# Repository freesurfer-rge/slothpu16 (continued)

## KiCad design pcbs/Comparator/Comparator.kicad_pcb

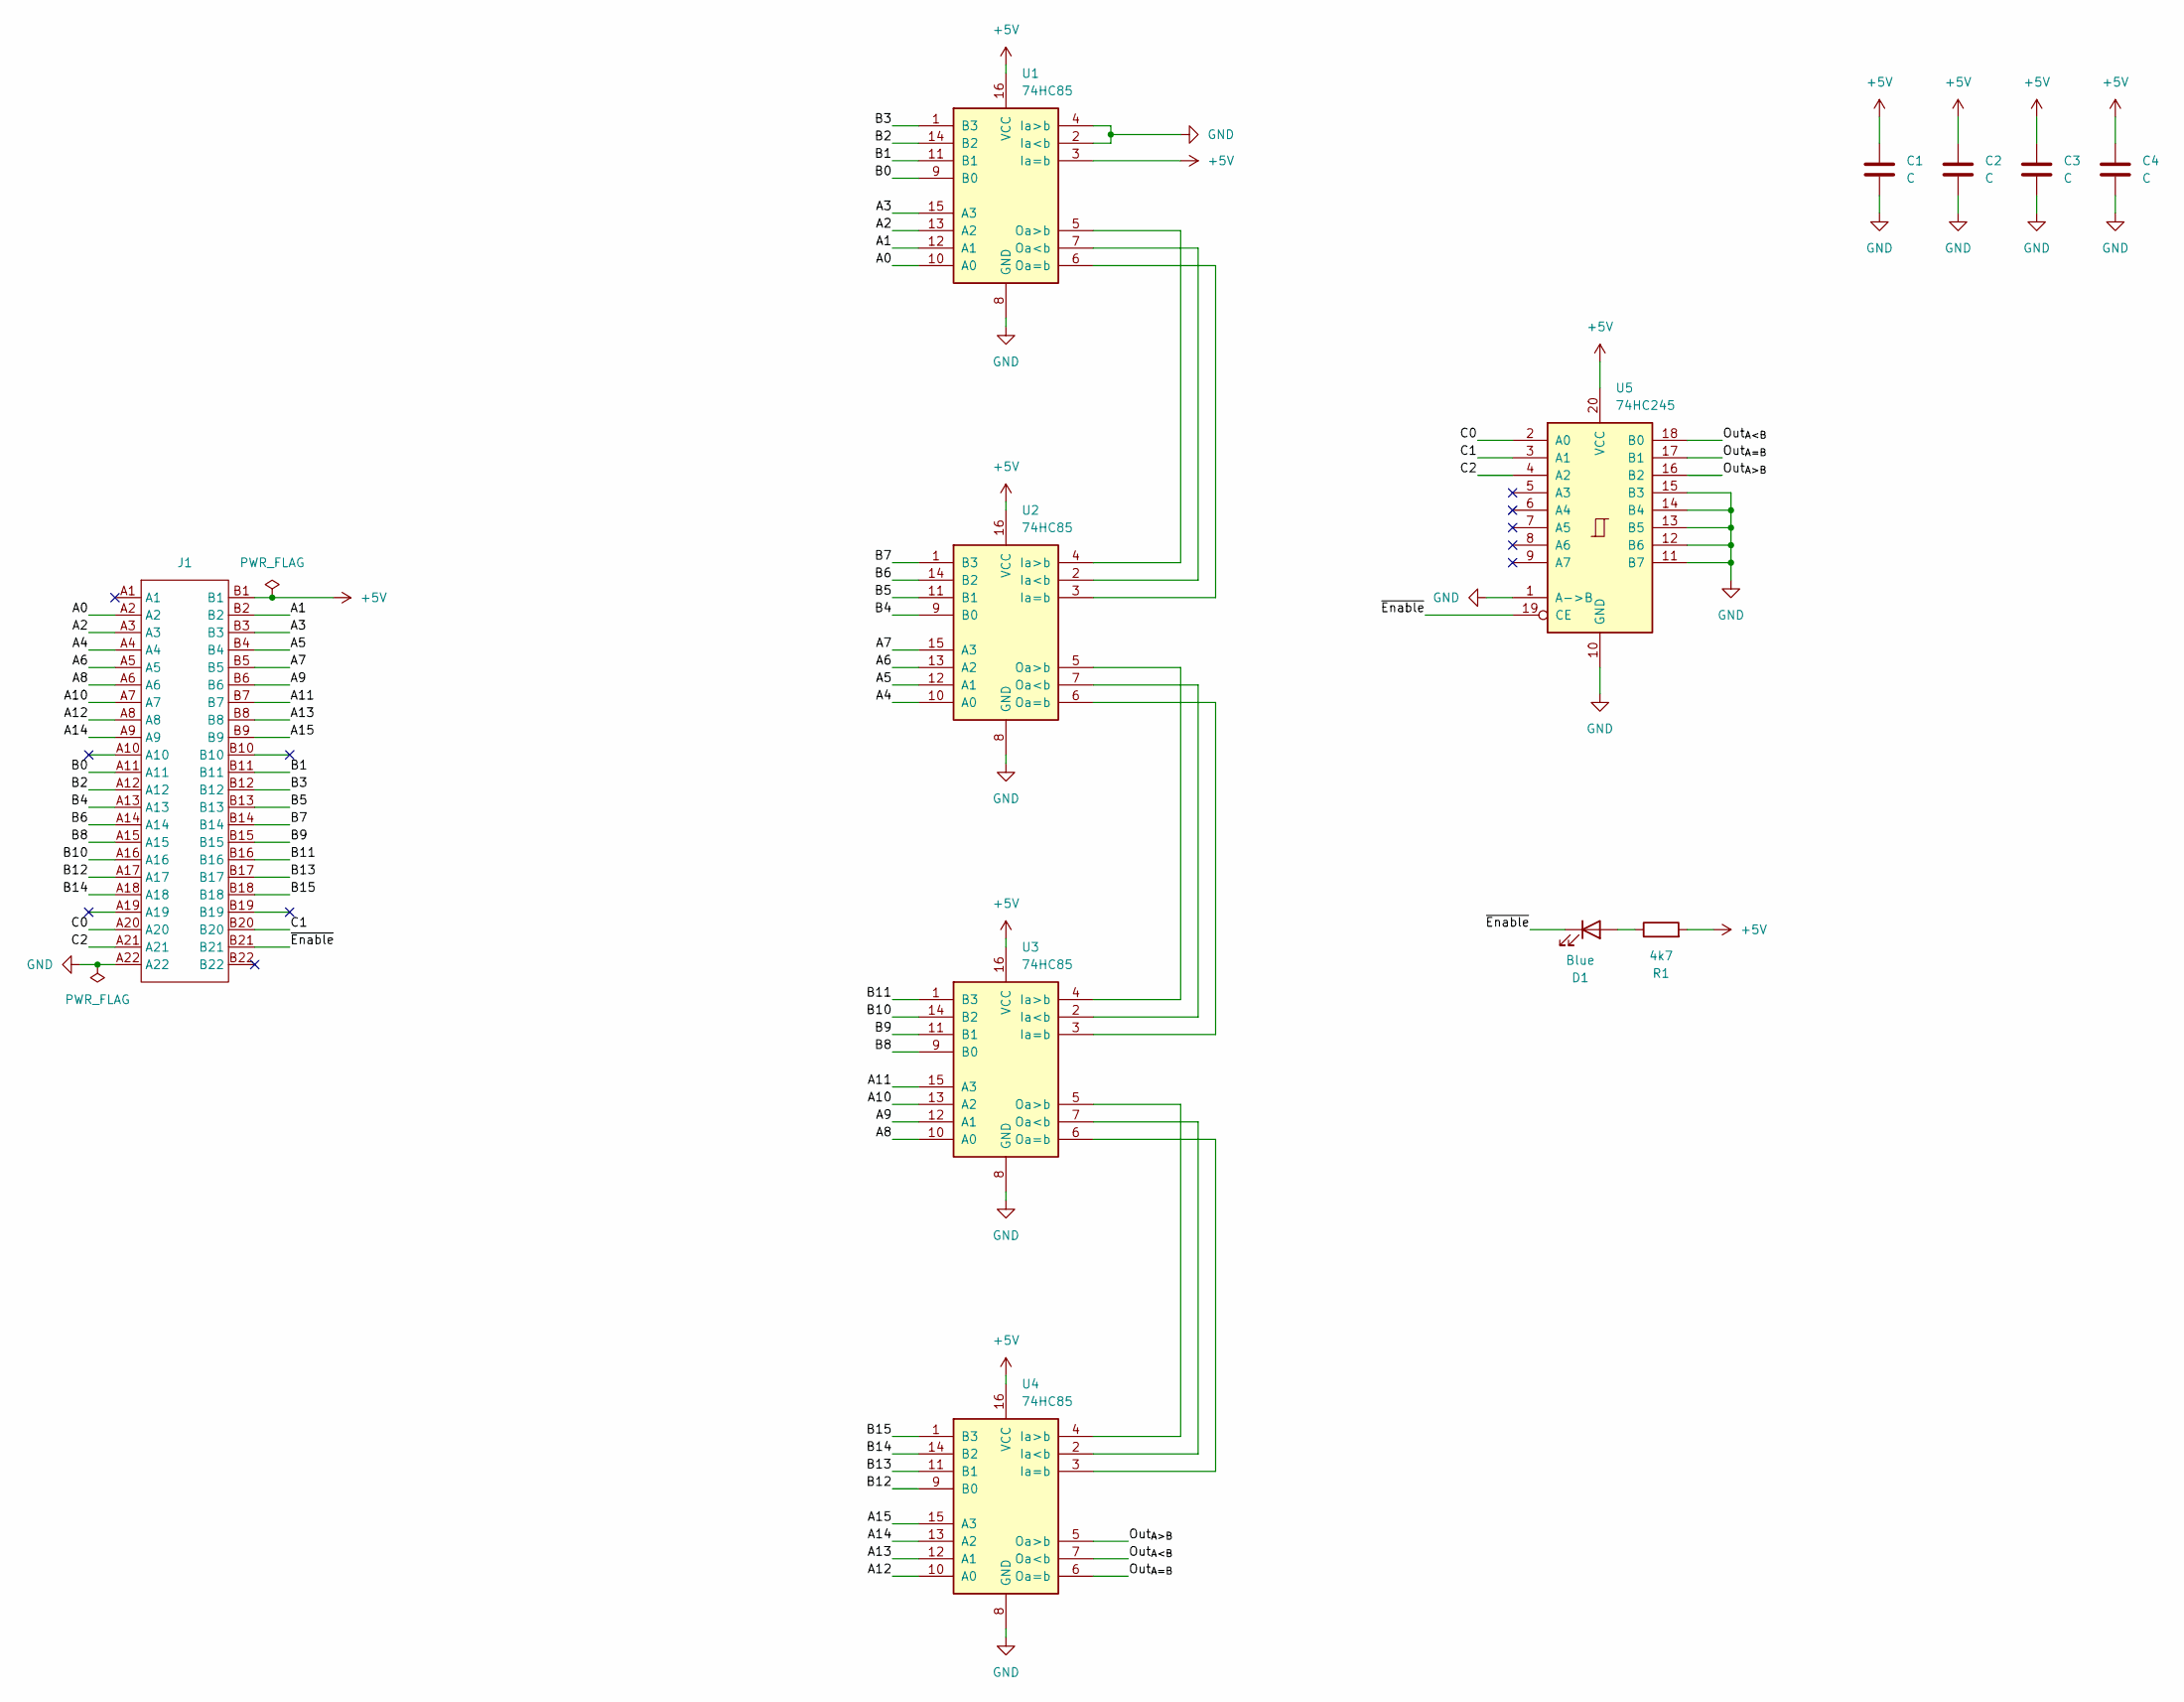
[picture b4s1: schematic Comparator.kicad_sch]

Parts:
C1, C2, C3, C4: C; C_0603_1608Metric; LCSC C14663
D1: Blue; LED_0603_1608Metric; LCSC C72041
J1: TE-5530843-4-Edge
R1: 4k7; R_0603_1608Metric; LCSC C23162
U1, U2, U3, U4: 74HC85; DIP-16_W7.62mm_Socket
U5: 74HC245; SOIC-20W_7.5x12.8mm_P1.27mm; LCSC C5625

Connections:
+5V: C1.1, C2.1, C3.1, C4.1, J1.B1, R1.2, U1.3 (Ia=b), U1.16 (VCC), U2.16 (VCC), U3.16 (VCC), U4.16 (VCC), U5.20 (VCC)
/A0: J1.A2, U1.10 (A0)
/A1: J1.B2, U1.12 (A1)
/A2: J1.A3, U1.13 (A2)
/A3: J1.B3, U1.15 (A3)
/A4: J1.A4, U2.10 (A0)
/A5: J1.B4, U2.12 (A1)
/A6: J1.A5, U2.13 (A2)
/A7: J1.B5, U2.15 (A3)
/A8: J1.A6, U3.10 (A0)
/A9: J1.B6, U3.12 (A1)
/A10: J1.A7, U3.13 (A2)
/A11: J1.B7, U3.15 (A3)
/A12: J1.A8, U4.10 (A0)
/A13: J1.B8, U4.12 (A1)
/A14: J1.A9, U4.13 (A2)
/A15: J1.B9, U4.15 (A3)
/B0: J1.A11, U1.9 (B0)
/B1: J1.B11, U1.11 (B1)
/B2: J1.A12, U1.14 (B2)
/B3: J1.B12, U1.1 (B3)
/B4: J1.A13, U2.9 (B0)
/B5: J1.B13, U2.11 (B1)
/B6: J1.A14, U2.14 (B2)
/B7: J1.B14, U2.1 (B3)
/B8: J1.A15, U3.9 (B0)
/B9: J1.B15, U3.11 (B1)
/B10: J1.A16, U3.14 (B2)
/B11: J1.B16, U3.1 (B3)
/B12: J1.A17, U4.9 (B0)
/B13: J1.B17, U4.11 (B1)
/B14: J1.A18, U4.14 (B2)
/B15: J1.B18, U4.1 (B3)
/C0: J1.A20, U5.2 (A0)
/C1: J1.B20, U5.3 (A1)
/C2: J1.A21, U5.4 (A2)
/Out_{A<B}: U4.7 (Oa<b), U5.18 (B0)
/Out_{A=B}: U4.6 (Oa=b), U5.17 (B1)
/Out_{A>B}: U4.5 (Oa>b), U5.16 (B2)
/~Enable: D1.1 (K), J1.B21, U5.19 (CE)
GND: C1.2, C2.2, C3.2, C4.2, J1.A22, U1.2 (Ia<b), U1.4 (Ia>b), U1.8 (GND), U2.8 (GND), U3.8 (GND), U4.8 (GND), U5.1 (A->B), U5.10 (GND), U5.11 (B7), U5.12 (B6), U5.13 (B5), U5.14 (B4), U5.15 (B3)
unnamed: D1.2 (A), R1.1
unnamed: U1.7 (Oa<b), U2.2 (Ia<b)
unnamed: U1.6 (Oa=b), U2.3 (Ia=b)
unnamed: U1.5 (Oa>b), U2.4 (Ia>b)
unnamed: U2.7 (Oa<b), U3.2 (Ia<b)
unnamed: U2.6 (Oa=b), U3.3 (Ia=b)
unnamed: U2.5 (Oa>b), U3.4 (Ia>b)
unnamed: U3.7 (Oa<b), U4.2 (Ia<b)
unnamed: U3.6 (Oa=b), U4.3 (Ia=b)
unnamed: U3.5 (Oa>b), U4.4 (Ia>b)

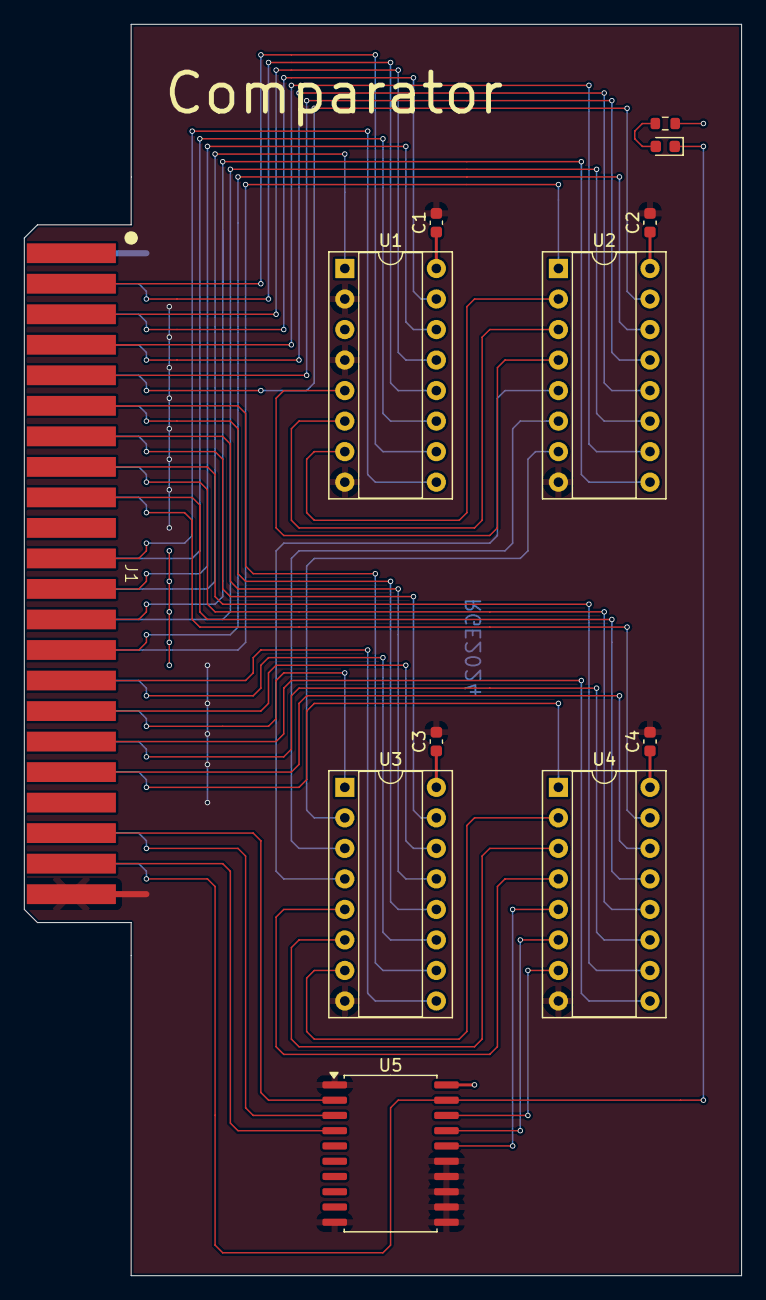
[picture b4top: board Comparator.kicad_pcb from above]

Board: 2 copper layers, 59.7 x 104.1 mm, 12 parts (0 on the bottom side), 51 nets.

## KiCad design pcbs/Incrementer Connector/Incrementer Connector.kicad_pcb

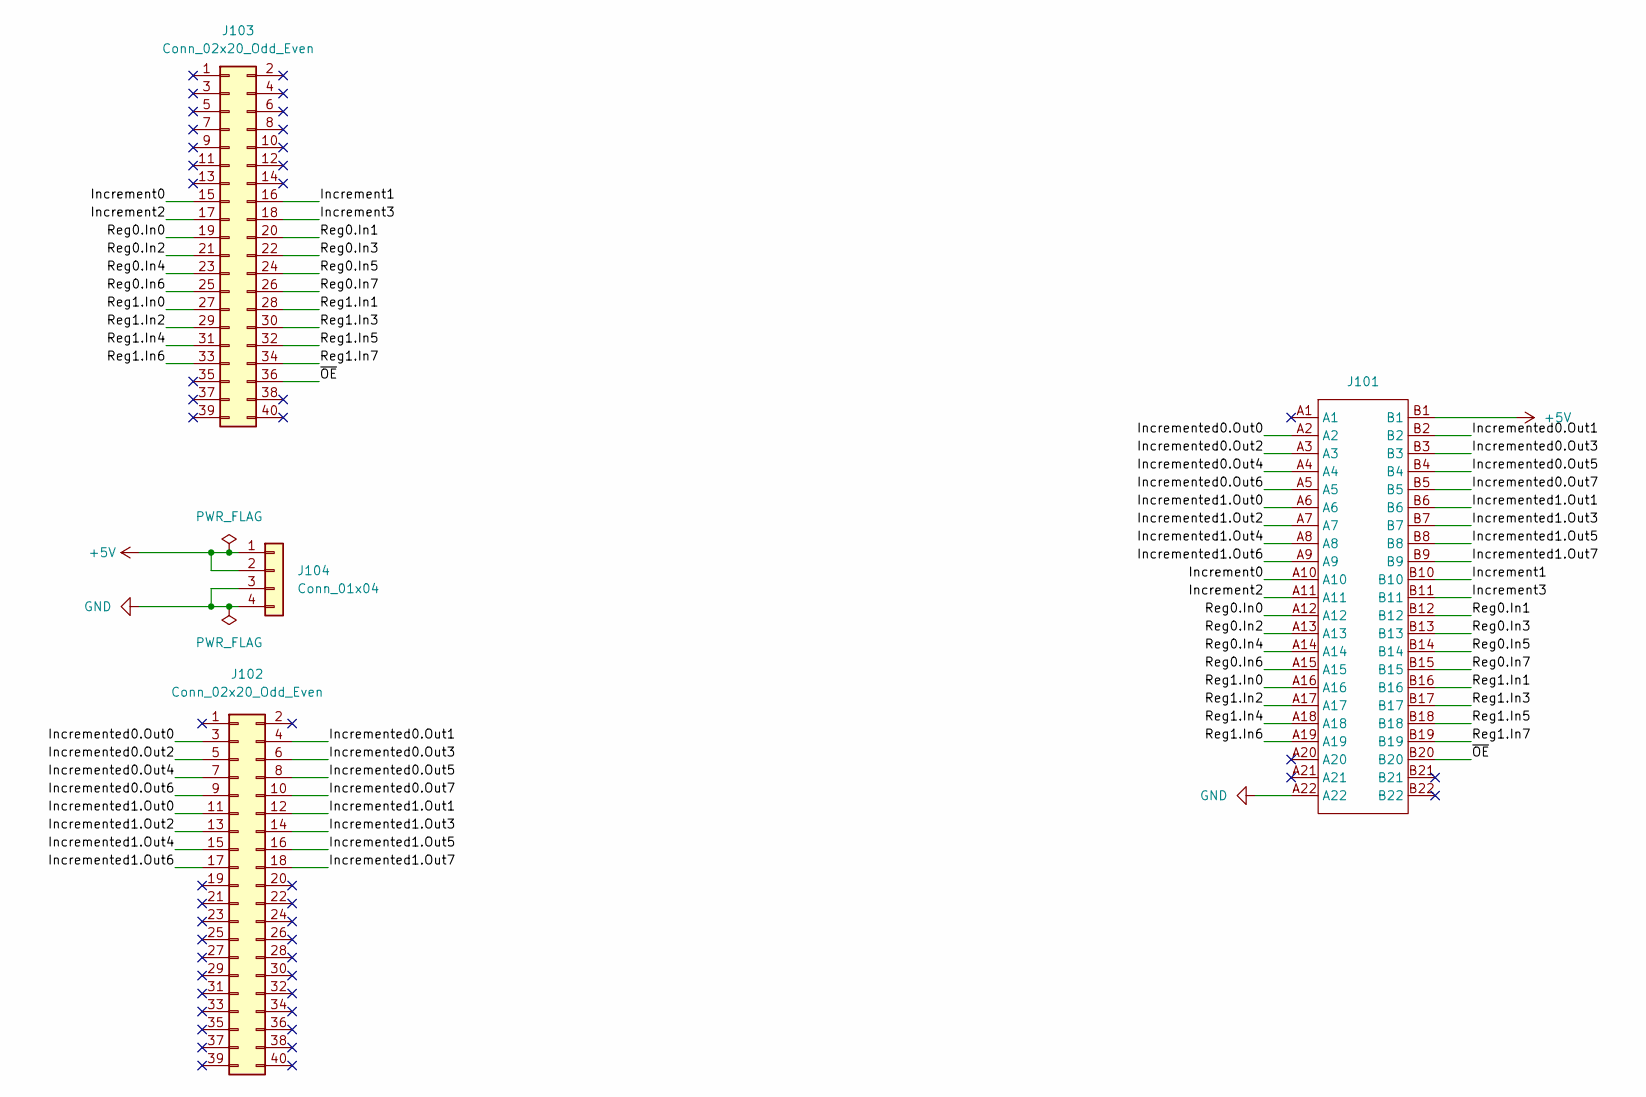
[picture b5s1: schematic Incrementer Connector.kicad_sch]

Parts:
J101: TE-5530843-4-Mount
J102, J103: Conn_02x20_Odd_Even; PinHeader_2x20_P2.54mm_Vertical
J104: Conn_01x04; PinHeader_1x04_P2.54mm_Vertical

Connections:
+5V: J101.B1, J104.1, J104.2
/Increment0: J101.A10, J103.15
/Increment1: J101.B10, J103.16
/Increment2: J101.A11, J103.17
/Increment3: J101.B11, J103.18
/Incremented0.Out0: J101.A2, J102.3
/Incremented0.Out1: J101.B2, J102.4
/Incremented0.Out2: J101.A3, J102.5
/Incremented0.Out3: J101.B3, J102.6
/Incremented0.Out4: J101.A4, J102.7
/Incremented0.Out5: J101.B4, J102.8
/Incremented0.Out6: J101.A5, J102.9
/Incremented0.Out7: J101.B5, J102.10
/Incremented1.Out0: J101.A6, J102.11
/Incremented1.Out1: J101.B6, J102.12
/Incremented1.Out2: J101.A7, J102.13
/Incremented1.Out3: J101.B7, J102.14
/Incremented1.Out4: J101.A8, J102.15
/Incremented1.Out5: J101.B8, J102.16
/Incremented1.Out6: J101.A9, J102.17
/Incremented1.Out7: J101.B9, J102.18
/Reg0.In0: J101.A12, J103.19
/Reg0.In1: J101.B12, J103.20
/Reg0.In2: J101.A13, J103.21
/Reg0.In3: J101.B13, J103.22
/Reg0.In4: J101.A14, J103.23
/Reg0.In5: J101.B14, J103.24
/Reg0.In6: J101.A15, J103.25
/Reg0.In7: J101.B15, J103.26
/Reg1.In0: J101.A16, J103.27
/Reg1.In1: J101.B16, J103.28
/Reg1.In2: J101.A17, J103.29
/Reg1.In3: J101.B17, J103.30
/Reg1.In4: J101.A18, J103.31
/Reg1.In5: J101.B18, J103.32
/Reg1.In6: J101.A19, J103.33
/Reg1.In7: J101.B19, J103.34
/~OE: J101.B20, J103.36
GND: J101.A22, J104.3, J104.4

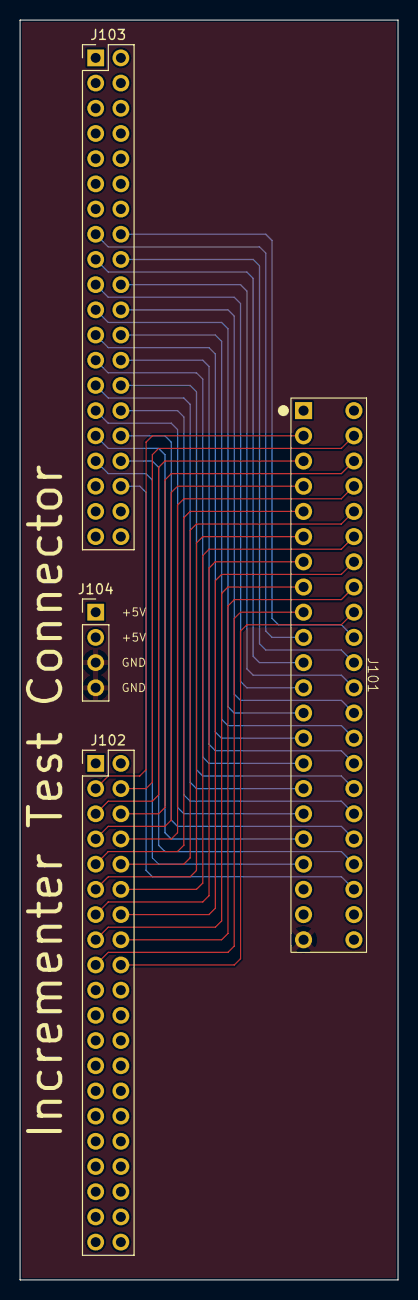
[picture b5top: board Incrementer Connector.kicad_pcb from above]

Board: 2 copper layers, 38.1 x 127.0 mm, 4 parts (0 on the bottom side), 39 nets.

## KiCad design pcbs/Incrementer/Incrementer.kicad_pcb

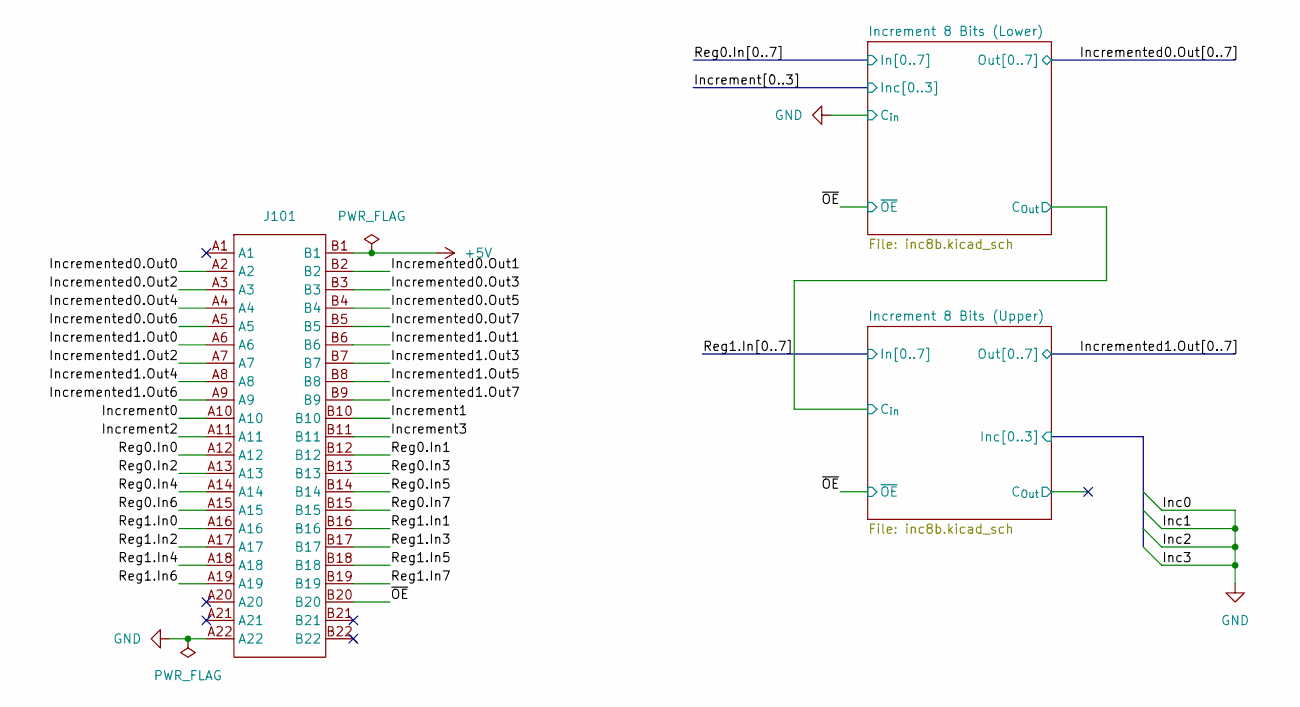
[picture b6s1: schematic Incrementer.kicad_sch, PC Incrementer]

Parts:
J101: TE-5530843-4-Edge

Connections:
+5V: J101.B1; also elsewhere on the board
/Increment0: J101.A10; also elsewhere on the board
/Increment1: J101.B10; also elsewhere on the board
/Increment2: J101.A11; also elsewhere on the board
/Increment3: J101.B11; also elsewhere on the board
/Incremented0.Out0: J101.A2; also elsewhere on the board
/Incremented0.Out1: J101.B2; also elsewhere on the board
/Incremented0.Out2: J101.A3; also elsewhere on the board
/Incremented0.Out3: J101.B3; also elsewhere on the board
/Incremented0.Out4: J101.A4; also elsewhere on the board
/Incremented0.Out5: J101.B4; also elsewhere on the board
/Incremented0.Out6: J101.A5; also elsewhere on the board
/Incremented0.Out7: J101.B5; also elsewhere on the board
/Incremented1.Out0: J101.A6; also elsewhere on the board
/Incremented1.Out1: J101.B6; also elsewhere on the board
/Incremented1.Out2: J101.A7; also elsewhere on the board
/Incremented1.Out3: J101.B7; also elsewhere on the board
/Incremented1.Out4: J101.A8; also elsewhere on the board
/Incremented1.Out5: J101.B8; also elsewhere on the board
/Incremented1.Out6: J101.A9; also elsewhere on the board
/Incremented1.Out7: J101.B9; also elsewhere on the board
/Reg0.In0: J101.A12; also elsewhere on the board
/Reg0.In1: J101.B12; also elsewhere on the board
/Reg0.In2: J101.A13; also elsewhere on the board
/Reg0.In3: J101.B13; also elsewhere on the board
/Reg0.In4: J101.A14; also elsewhere on the board
/Reg0.In5: J101.B14; also elsewhere on the board
/Reg0.In6: J101.A15; also elsewhere on the board
/Reg0.In7: J101.B15; also elsewhere on the board
/Reg1.In0: J101.A16; also elsewhere on the board
/Reg1.In1: J101.B16; also elsewhere on the board
/Reg1.In2: J101.A17; also elsewhere on the board
/Reg1.In3: J101.B17; also elsewhere on the board
/Reg1.In4: J101.A18; also elsewhere on the board
/Reg1.In5: J101.B18; also elsewhere on the board
/Reg1.In6: J101.A19; also elsewhere on the board
/Reg1.In7: J101.B19; also elsewhere on the board
/~OE: J101.B20; also elsewhere on the board
GND: J101.A22; also elsewhere on the board

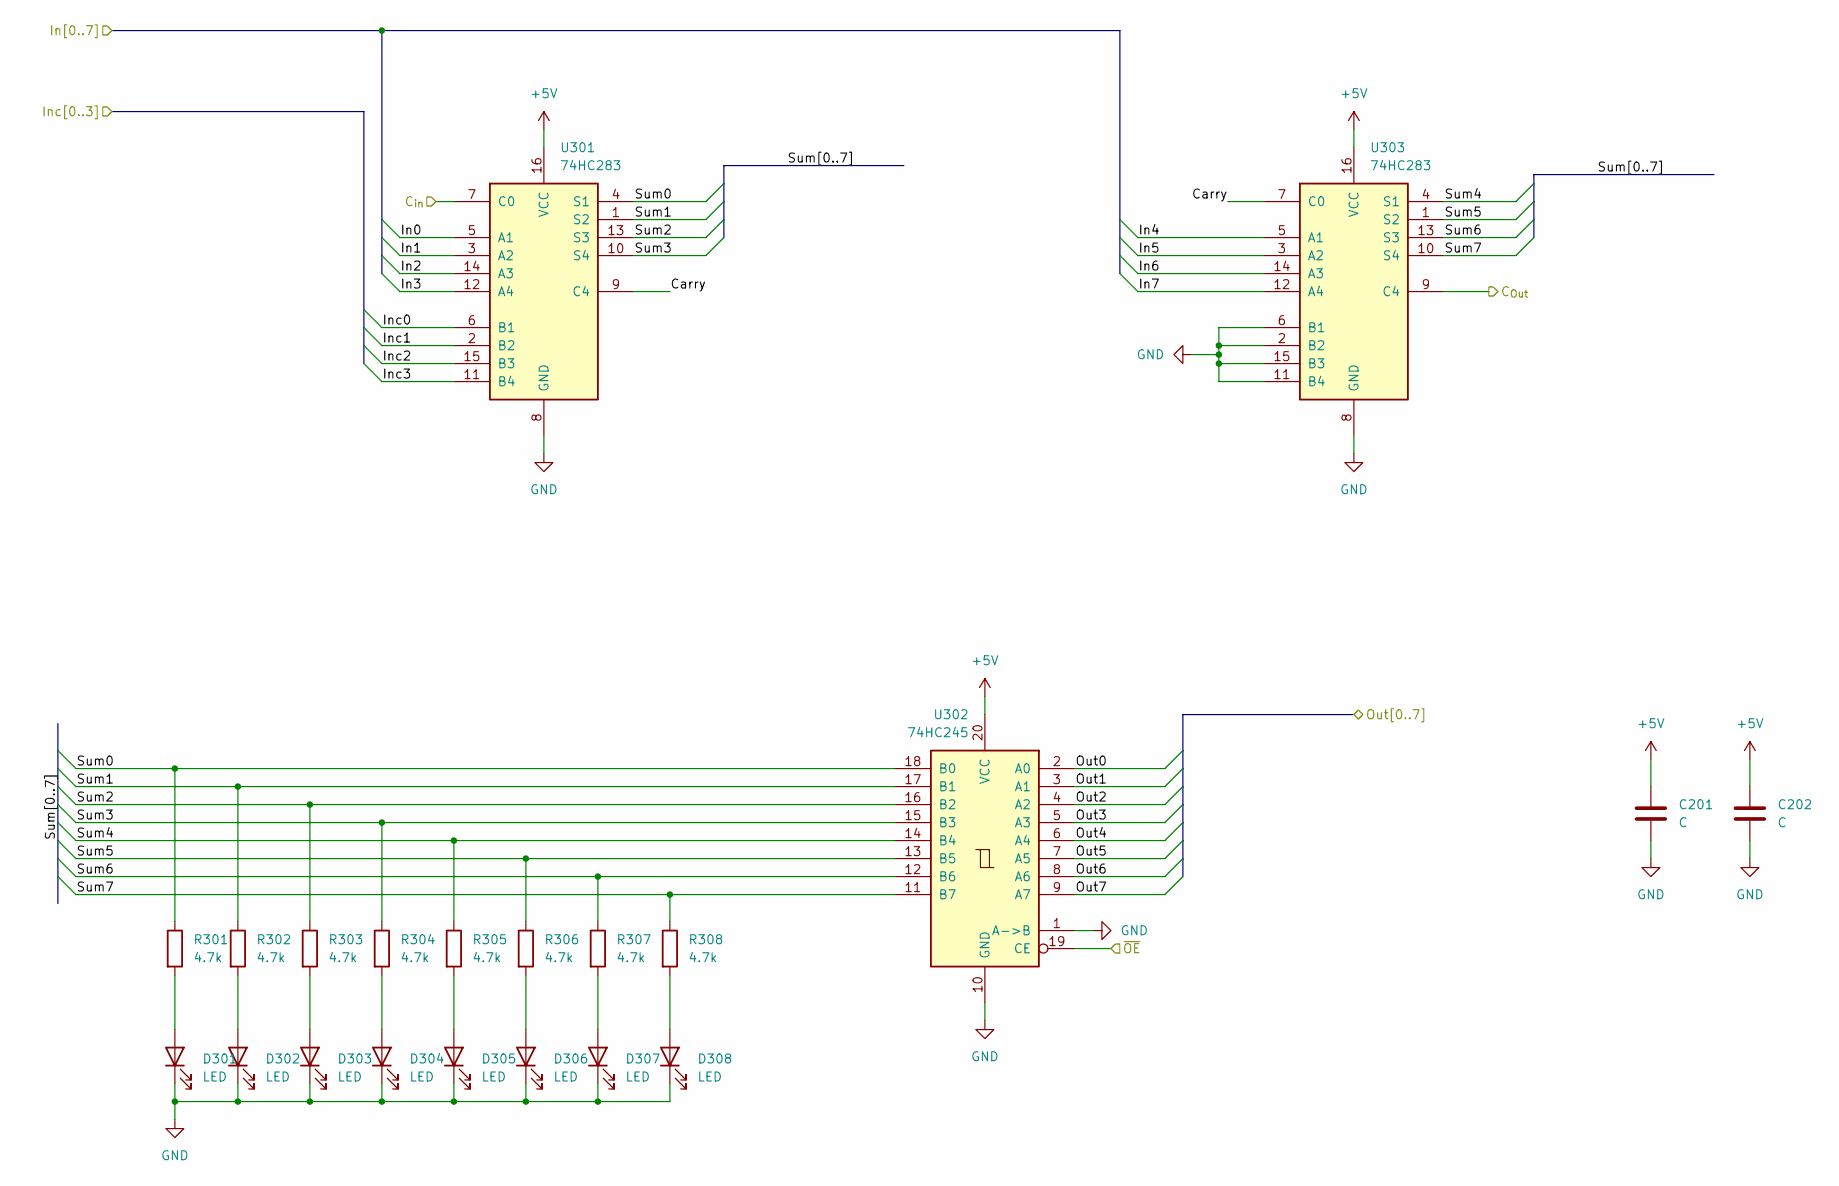
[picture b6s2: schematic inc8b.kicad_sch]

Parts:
C201, C202: C; C_0603_1608Metric; LCSC C14663
D301, D302, D303, D304, D305, D306, D307, D308: LED; LED_0603_1608Metric; LCSC C2290
R301, R302, R303, R304, R305, R306, R307, R308: 4.7k; R_0603_1608Metric; LCSC C23162
U301, U303: 74HC283; DIP-16_W7.62mm_Socket
U302: 74HC245; SOIC-20W_7.5x12.8mm_P1.27mm; LCSC C5625

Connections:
+5V: C201.1, C202.1, U301.16 (VCC), U302.20 (VCC), U303.16 (VCC); also elsewhere on the board
/Increment 8 Bits (Lower)/C_{Out}: U301.7 (C0); also elsewhere on the board
/Increment 8 Bits (Upper)/C_{Out}: U303.9 (C4)
/Increment 8 Bits (Upper)/Carry: U301.9 (C4), U303.7 (C0)
/Increment 8 Bits (Upper)/Sum0: R301.1, U301.4 (S1), U302.18 (B0)
/Increment 8 Bits (Upper)/Sum1: R302.1, U301.1 (S2), U302.17 (B1)
/Increment 8 Bits (Upper)/Sum2: R303.1, U301.13 (S3), U302.16 (B2)
/Increment 8 Bits (Upper)/Sum3: R304.1, U301.10 (S4), U302.15 (B3)
/Increment 8 Bits (Upper)/Sum4: R305.1, U302.14 (B4), U303.4 (S1)
/Increment 8 Bits (Upper)/Sum5: R306.1, U302.13 (B5), U303.1 (S2)
/Increment 8 Bits (Upper)/Sum6: R307.1, U302.12 (B6), U303.13 (S3)
/Increment 8 Bits (Upper)/Sum7: R308.1, U302.11 (B7), U303.10 (S4)
/Incremented1.Out0: U302.2 (A0); also elsewhere on the board
/Incremented1.Out1: U302.3 (A1); also elsewhere on the board
/Incremented1.Out2: U302.4 (A2); also elsewhere on the board
/Incremented1.Out3: U302.5 (A3); also elsewhere on the board
/Incremented1.Out4: U302.6 (A4); also elsewhere on the board
/Incremented1.Out5: U302.7 (A5); also elsewhere on the board
/Incremented1.Out6: U302.8 (A6); also elsewhere on the board
/Incremented1.Out7: U302.9 (A7); also elsewhere on the board
/Reg1.In0: U301.5 (A1); also elsewhere on the board
/Reg1.In1: U301.3 (A2); also elsewhere on the board
/Reg1.In2: U301.14 (A3); also elsewhere on the board
/Reg1.In3: U301.12 (A4); also elsewhere on the board
/Reg1.In4: U303.5 (A1); also elsewhere on the board
/Reg1.In5: U303.3 (A2); also elsewhere on the board
/Reg1.In6: U303.14 (A3); also elsewhere on the board
/Reg1.In7: U303.12 (A4); also elsewhere on the board
/~OE: U302.19 (CE); also elsewhere on the board
GND: C201.2, C202.2, D301.1 (K), D302.1 (K), D303.1 (K), D304.1 (K), D305.1 (K), D306.1 (K), D307.1 (K), D308.1 (K), U301.2 (B2), U301.6 (B1), U301.8 (GND), U301.11 (B4), U301.15 (B3), U302.1 (A->B), U302.10 (GND), U303.2 (B2), U303.6 (B1), U303.8 (GND), U303.11 (B4), U303.15 (B3); also elsewhere on the board
unnamed: D301.2 (A), R301.2
unnamed: D302.2 (A), R302.2
unnamed: D303.2 (A), R303.2
unnamed: D304.2 (A), R304.2
unnamed: D305.2 (A), R305.2
unnamed: D306.2 (A), R306.2
unnamed: D307.2 (A), R307.2
unnamed: D308.2 (A), R308.2

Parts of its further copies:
C301, C302: C; C_0603_1608Metric; LCSC C14663
D201, D202, D203, D204, D205, D206, D207, D208: LED; LED_0603_1608Metric; LCSC C2290
R201, R202, R203, R204, R205, R206, R207, R208: 4.7k; R_0603_1608Metric; LCSC C23162
U201, U203: 74HC283; DIP-16_W7.62mm_Socket
U202: 74HC245; SOIC-20W_7.5x12.8mm_P1.27mm; LCSC C5625

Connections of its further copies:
+5V: C301.1, C302.1, U201.16 (VCC), U202.20 (VCC), U203.16 (VCC); also elsewhere on the board
/Increment0: U201.6 (B1); also elsewhere on the board
/Increment1: U201.2 (B2); also elsewhere on the board
/Increment2: U201.15 (B3); also elsewhere on the board
/Increment3: U201.11 (B4); also elsewhere on the board
/Increment 8 Bits (Lower)/C_{Out}: U203.9 (C4); also elsewhere on the board
/Increment 8 Bits (Lower)/Carry: U201.9 (C4), U203.7 (C0)
/Increment 8 Bits (Lower)/Sum0: R201.1, U201.4 (S1), U202.18 (B0)
/Increment 8 Bits (Lower)/Sum1: R202.1, U201.1 (S2), U202.17 (B1)
/Increment 8 Bits (Lower)/Sum2: R203.1, U201.13 (S3), U202.16 (B2)
/Increment 8 Bits (Lower)/Sum3: R204.1, U201.10 (S4), U202.15 (B3)
/Increment 8 Bits (Lower)/Sum4: R205.1, U202.14 (B4), U203.4 (S1)
/Increment 8 Bits (Lower)/Sum5: R206.1, U202.13 (B5), U203.1 (S2)
/Increment 8 Bits (Lower)/Sum6: R207.1, U202.12 (B6), U203.13 (S3)
/Increment 8 Bits (Lower)/Sum7: R208.1, U202.11 (B7), U203.10 (S4)
/Incremented0.Out0: U202.2 (A0); also elsewhere on the board
/Incremented0.Out1: U202.3 (A1); also elsewhere on the board
/Incremented0.Out2: U202.4 (A2); also elsewhere on the board
/Incremented0.Out3: U202.5 (A3); also elsewhere on the board
/Incremented0.Out4: U202.6 (A4); also elsewhere on the board
/Incremented0.Out5: U202.7 (A5); also elsewhere on the board
/Incremented0.Out6: U202.8 (A6); also elsewhere on the board
/Incremented0.Out7: U202.9 (A7); also elsewhere on the board
/Reg0.In0: U201.5 (A1); also elsewhere on the board
/Reg0.In1: U201.3 (A2); also elsewhere on the board
/Reg0.In2: U201.14 (A3); also elsewhere on the board
/Reg0.In3: U201.12 (A4); also elsewhere on the board
/Reg0.In4: U203.5 (A1); also elsewhere on the board
/Reg0.In5: U203.3 (A2); also elsewhere on the board
/Reg0.In6: U203.14 (A3); also elsewhere on the board
/Reg0.In7: U203.12 (A4); also elsewhere on the board
/~OE: U202.19 (CE); also elsewhere on the board
GND: C301.2, C302.2, D201.1 (K), D202.1 (K), D203.1 (K), D204.1 (K), D205.1 (K), D206.1 (K), D207.1 (K), D208.1 (K), U201.7 (C0), U201.8 (GND), U202.1 (A->B), U202.10 (GND), U203.2 (B2), U203.6 (B1), U203.8 (GND), U203.11 (B4), U203.15 (B3); also elsewhere on the board
unnamed: D201.2 (A), R201.2
unnamed: D202.2 (A), R202.2
unnamed: D203.2 (A), R203.2
unnamed: D204.2 (A), R204.2
unnamed: D205.2 (A), R205.2
unnamed: D206.2 (A), R206.2
unnamed: D207.2 (A), R207.2
unnamed: D208.2 (A), R208.2

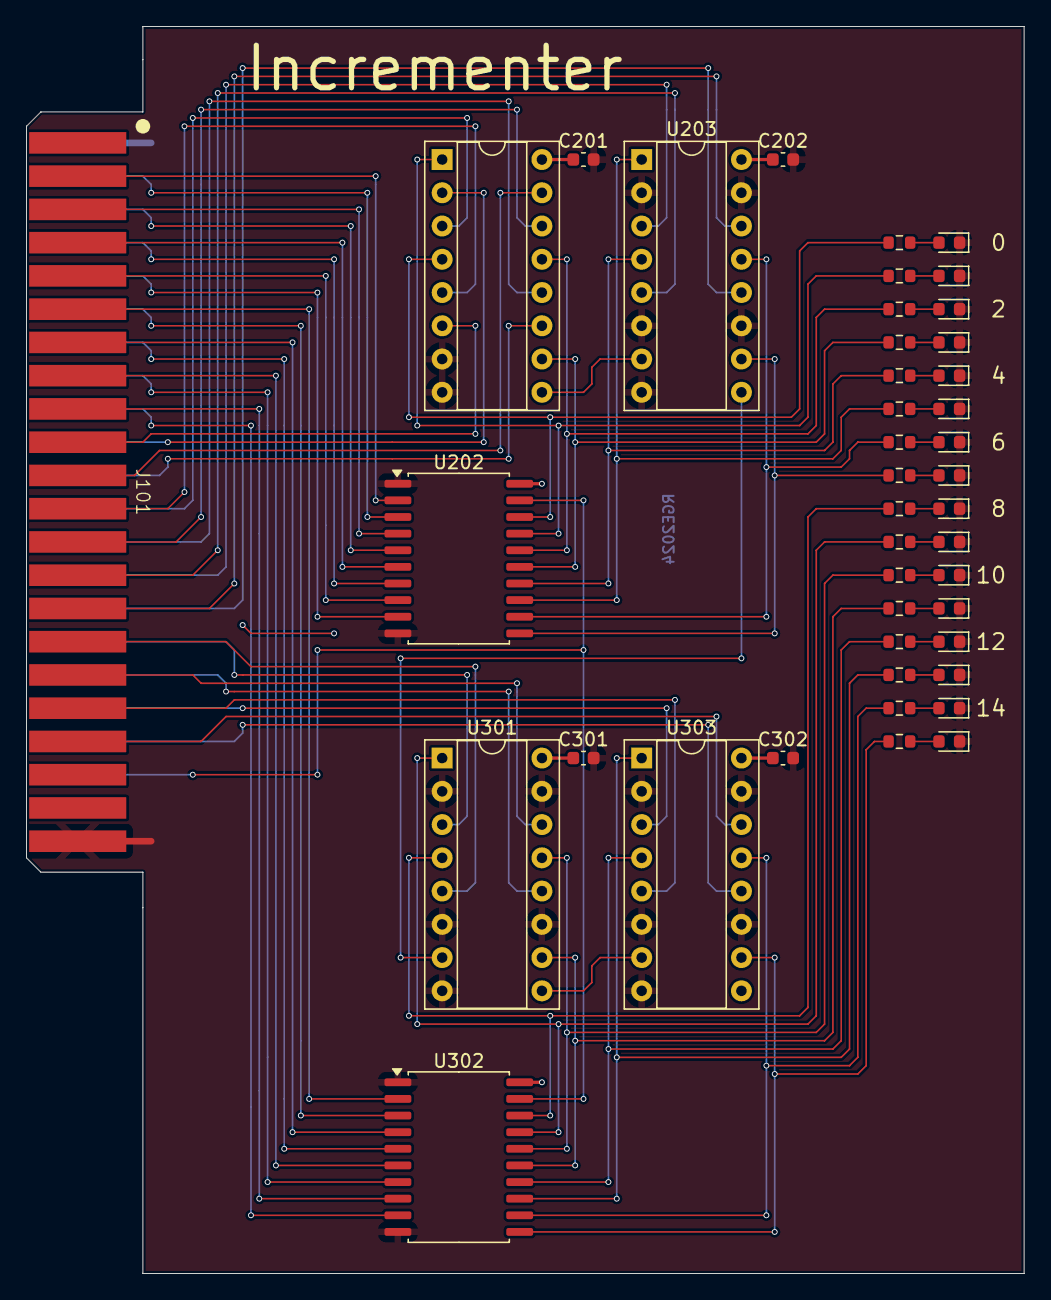
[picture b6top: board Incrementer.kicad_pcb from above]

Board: 2 copper layers, 76.2 x 95.2 mm, 43 parts (0 on the bottom side), 74 nets.

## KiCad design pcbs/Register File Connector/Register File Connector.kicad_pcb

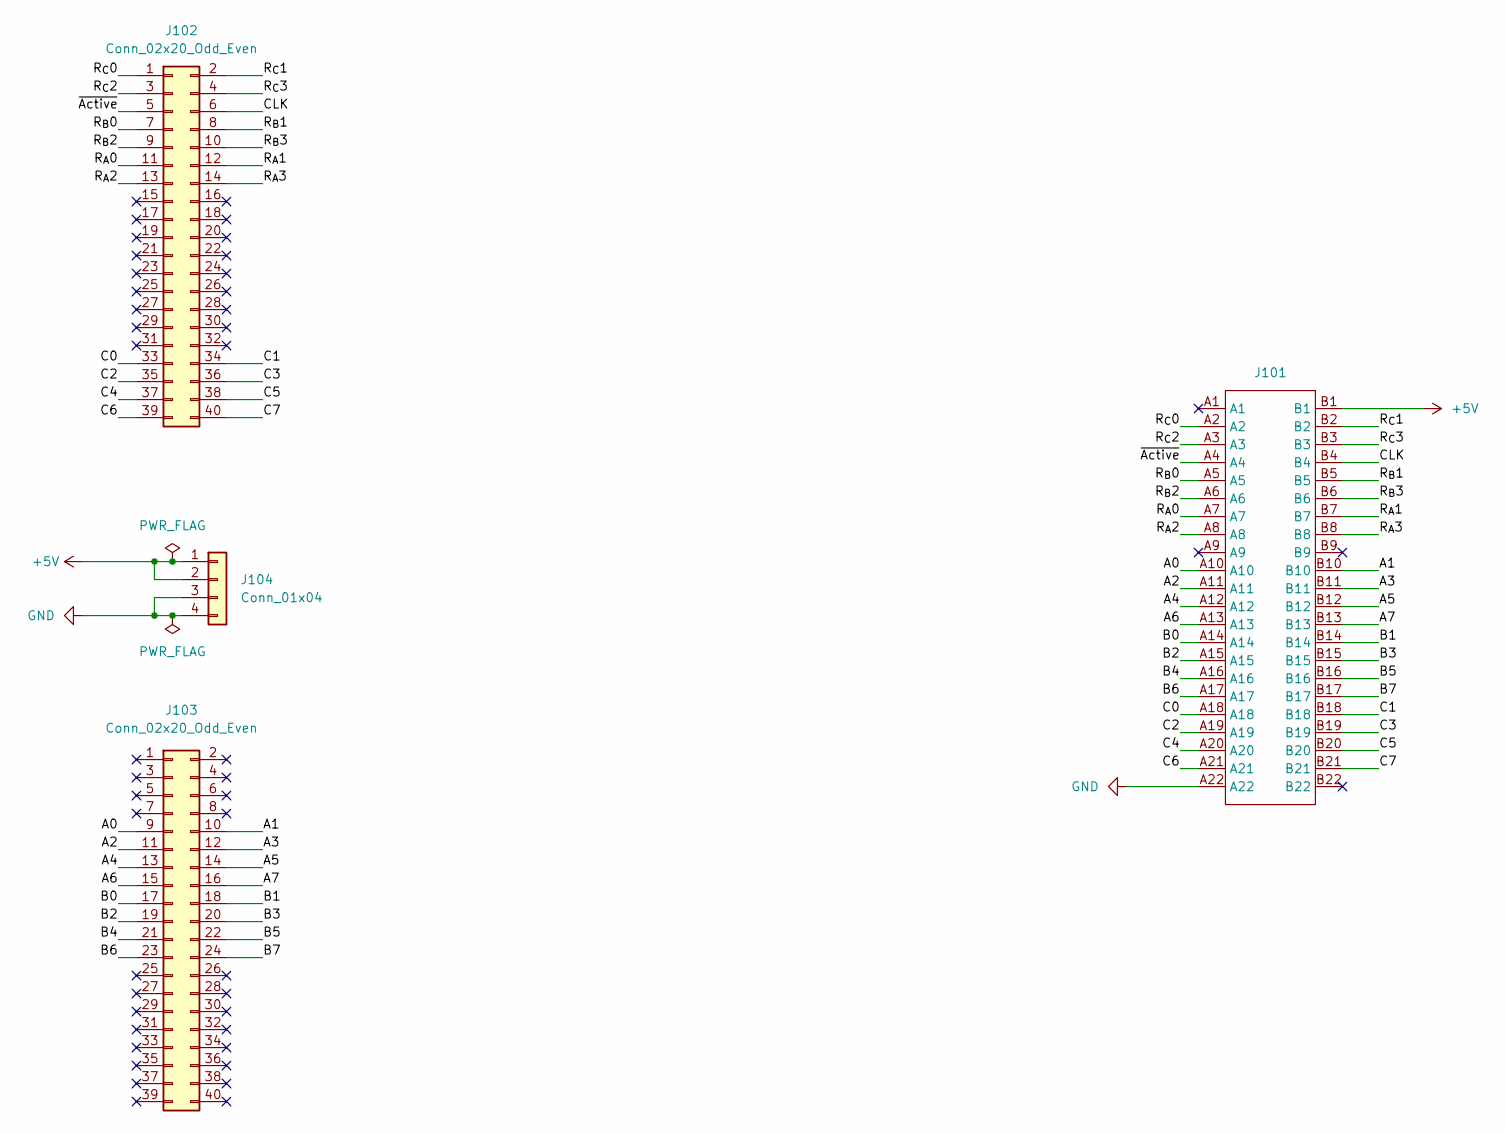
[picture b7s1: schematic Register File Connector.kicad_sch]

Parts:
J101: TE-5530843-4-Mount
J102, J103: Conn_02x20_Odd_Even; PinHeader_2x20_P2.54mm_Vertical
J104: Conn_01x04; PinHeader_1x04_P2.54mm_Vertical

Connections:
+5V: J101.B1, J104.1, J104.2
/A0: J101.A10, J103.9
/A1: J101.B10, J103.10
/A2: J101.A11, J103.11
/A3: J101.B11, J103.12
/A4: J101.A12, J103.13
/A5: J101.B12, J103.14
/A6: J101.A13, J103.15
/A7: J101.B13, J103.16
/B0: J101.A14, J103.17
/B1: J101.B14, J103.18
/B2: J101.A15, J103.19
/B3: J101.B15, J103.20
/B4: J101.A16, J103.21
/B5: J101.B16, J103.22
/B6: J101.A17, J103.23
/B7: J101.B17, J103.24
/C0: J101.A18, J102.33
/C1: J101.B18, J102.34
/C2: J101.A19, J102.35
/C3: J101.B19, J102.36
/C4: J101.A20, J102.37
/C5: J101.B20, J102.38
/C6: J101.A21, J102.39
/C7: J101.B21, J102.40
/CLK: J101.B4, J102.6
/R_{A}0: J101.A7, J102.11
/R_{A}1: J101.B7, J102.12
/R_{A}2: J101.A8, J102.13
/R_{A}3: J101.B8, J102.14
/R_{B}0: J101.A5, J102.7
/R_{B}1: J101.B5, J102.8
/R_{B}2: J101.A6, J102.9
/R_{B}3: J101.B6, J102.10
/R_{C}0: J101.A2, J102.1
/R_{C}1: J101.B2, J102.2
/R_{C}2: J101.A3, J102.3
/R_{C}3: J101.B3, J102.4
/~Active: J101.A4, J102.5
GND: J101.A22, J104.3, J104.4

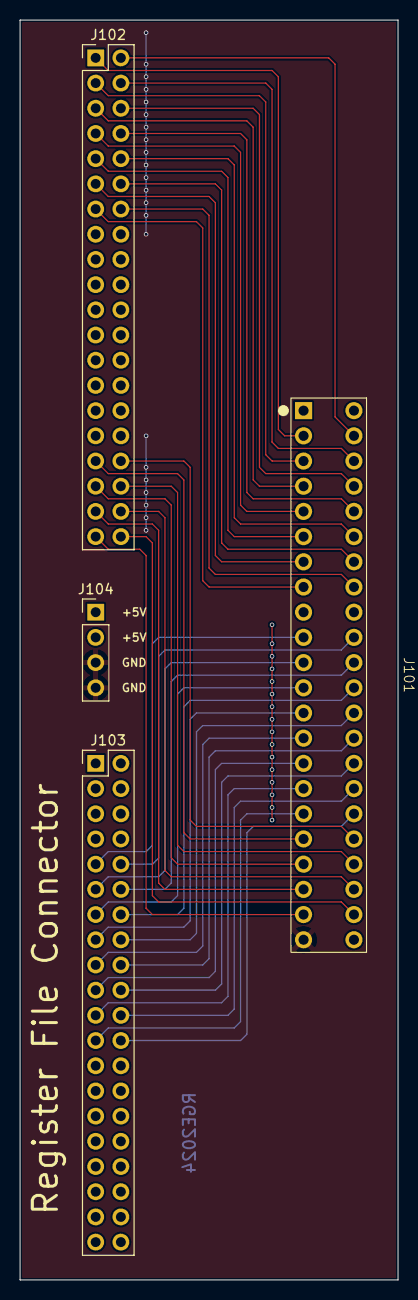
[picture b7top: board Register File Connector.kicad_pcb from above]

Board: 2 copper layers, 38.1 x 127.0 mm, 4 parts (0 on the bottom side), 40 nets.
